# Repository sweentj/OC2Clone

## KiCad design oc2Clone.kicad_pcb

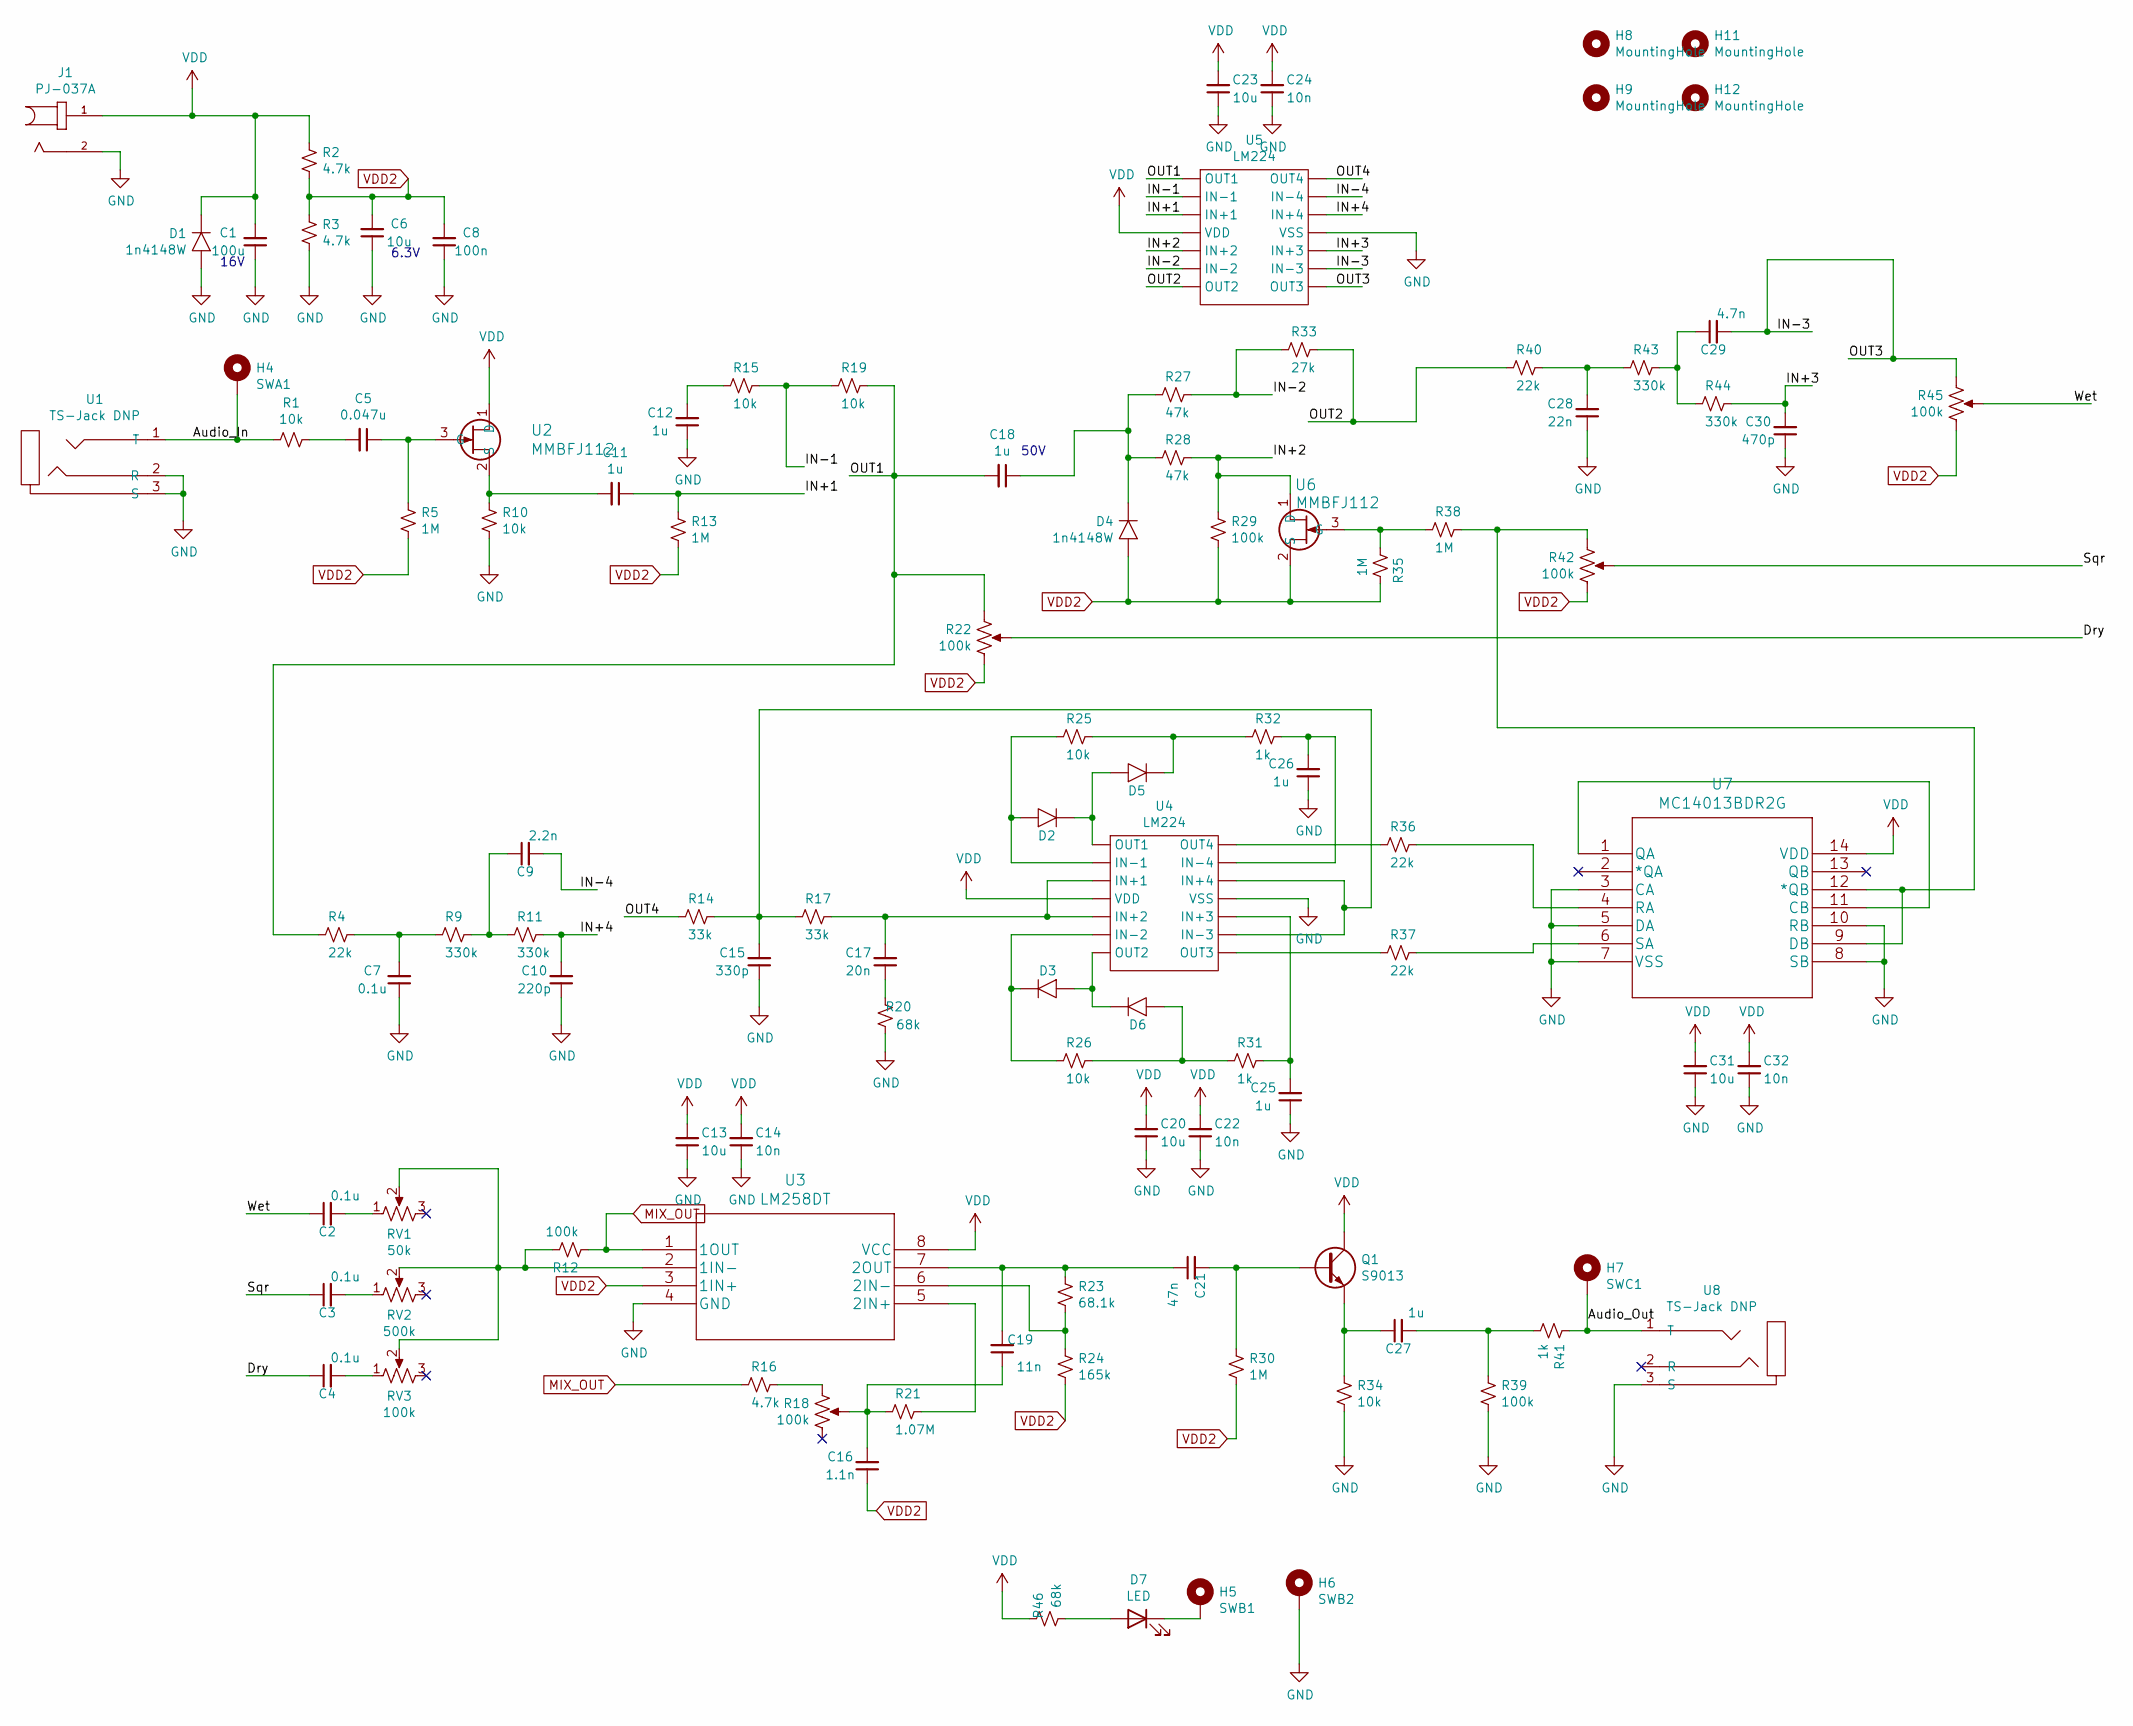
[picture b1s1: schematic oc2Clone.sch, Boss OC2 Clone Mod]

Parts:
C1: 100u; C_1210_3225Metric
C2, C3, C4, C7: 0.1u; C_0805_2012Metric
C5: 0.047u; C_0805_2012Metric
C6, C13, C20, C23, C31: 10u; C_0805_2012Metric
C8: 100n; C_0805_2012Metric
C9: 2.2n; C_0805_2012Metric
C10: 220p; C_0805_2012Metric
C11, C12, C18, C25, C26, C27: 1u; C_0805_2012Metric
C14, C22, C24, C32: 10n; C_0805_2012Metric
C15: 330p; C_0805_2012Metric
C16: 1.1n; C_0805_2012Metric
C17: 20n; C_0805_2012Metric
C19: 11n; C_0805_2012Metric
C21: 47n; C_0805_2012Metric
C28: 22n; C_0805_2012Metric
C29: 4.7n; C_0805_2012Metric
C30: 470p; C_0805_2012Metric
D1, D2, D3, D4, D5, D6: 1n4148W; SOD-123
D7: LED; LED_3mm_Radial
H4: SWA1; MountingHole_2.5mm_Pad
H5: SWB1; MountingHole_2.5mm_Pad
H6: SWB2; MountingHole_2.5mm_Pad
H7: SWC1; MountingHole_2.5mm_Pad
H8, H9, H11, H12: MountingHole; MountingHole_3.2mm_M3
J1: PJ-037A; CUI_PJ-037A
Q1: S9013; SOT-23
R1, R10, R15, R19, R25, R26, R34: 10k; R_0805_2012Metric
R2, R3, R16: 4.7k; R_0805_2012Metric
R4, R36, R37, R40: 22k; R_0805_2012Metric
R5, R13, R30, R35, R38: 1M; R_0805_2012Metric
R9, R11, R43, R44: 330k; R_0805_2012Metric
R12, R29, R39: 100k; R_0805_2012Metric
R14, R17: 33k; R_0805_2012Metric
R18, R22, R42, R45: 100k; Pot_RV16AF_Conn
R20, R46: 68k; R_0805_2012Metric
R21: 1.07M; R_0805_2012Metric
R23: 68.1k; R_0805_2012Metric
R24: 165k; R_0805_2012Metric
R27, R28: 47k; R_0805_2012Metric
R31, R32, R41: 1k; R_0805_2012Metric
R33: 27k; R_0805_2012Metric
RV1: 50k; Potentiometer_Bourns_TC33X_Vertical
RV2: 500k; Potentiometer_Bourns_TC33X_Vertical
RV3: 100k; Potentiometer_Bourns_TC33X_Vertical
U1, U8: TS-Jack DNP; TS-Jack
U2, U6: MMBFJ112; SOT-23
U3: LM258DT
U4, U5: LM224; SOIC-14_W3.9mm
U7: MC14013BDR2G; SOIC-14_W3.9mm

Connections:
/Audio_In: H4.1, R1.2, U1.1 (T)
/Audio_Out: H7.1, R41.2, U8.1 (T)
/Dry: C4.1, R22.2
/IN+1: C11.1, R13.2, U5.3 (IN+1)
/IN+2: R28.2, R29.2, U5.5 (IN+2), U6.1 (D)
/IN+3: C30.2, R44.2, U5.10 (IN+3)
/IN+4: C10.2, R11.2, U5.12 (IN+4)
/IN-1: R15.2, R19.1, U5.2 (IN-1)
/IN-2: R27.2, R33.1, U5.6 (IN-2)
/IN-3: C29.2, R45.1, U5.8 (OUT3), U5.9 (IN-3)
/IN-4: C9.2, U5.13 (IN-4)
/OUT1: C18.2, R4.1, R19.2, R22.1, U5.1 (OUT1)
/OUT2: R33.2, R40.1, U5.7 (OUT2)
/OUT4: R14.1, U5.14 (OUT4)
/Sqr: C3.1, R42.2
/Wet: C2.1, R45.2
GND: C1.1, C6.1, C7.1, C8.1, C10.1, C12.1, C13.1, C14.1, C15.1, C20.1, C22.1, C23.1, C24.1, C25.1, C26.1, C28.1, C30.1, C31.1, C32.1, D1.2, H6.1, J1.2, R3.1, R10.1, R20.2, R34.1, R39.1, U1.2 (R), U1.3 (S), U3.4 (GND), U4.11 (VSS), U5.11 (VSS), U7.3 (CA), U7.5 (DA), U7.7 (VSS), U7.8 (SB), U7.10 (RB), U8.3 (S)
MIX_OUT: R12.1, R16.1, U3.1 (1OUT)
unnamed: C2.2, RV1.1
unnamed: C3.2, RV2.1
unnamed: C4.2, RV3.1
unnamed: C5.1, R5.2, U2.3 (G)
unnamed: C5.2, R1.1
unnamed: C7.2, R4.2, R9.1
unnamed: C9.1, R9.2, R11.1
unnamed: C11.2, R10.2, U2.2 (S)
unnamed: C12.2, R15.1
unnamed: C15.2, R14.2, R17.1, U4.9 (IN-3), U4.12 (IN+4)
unnamed: C16.2, C19.1, R18.2, R21.1
unnamed: C17.1, R20.1
unnamed: C17.2, R17.2, U4.3 (IN+1), U4.5 (IN+2)
unnamed: C18.1, D4.1, R27.1, R28.1
unnamed: C19.2, C21.1, R23.2, U3.7 (2OUT)
unnamed: C21.2, Q1.1 (BASE_), R30.2
unnamed: C25.2, R31.2, U4.10 (IN+3)
unnamed: C26.2, R32.2, U4.13 (IN-4)
unnamed: C27.1, Q1.2 (EMITTER), R34.2
unnamed: C27.2, R39.2, R41.1
unnamed: C28.2, R40.2, R43.1
unnamed: C29.1, R43.2, R44.1
unnamed: D2.1, D5.2, U4.1 (OUT1)
unnamed: D2.2, R25.1, U4.2 (IN-1)
unnamed: D3.1, R26.1, U4.6 (IN-2)
unnamed: D3.2, D6.1, U4.7 (OUT2)
unnamed: D5.1, R25.2, R32.1
unnamed: D6.2, R26.2, R31.1
unnamed: D7.1 (K), H5.1
unnamed: D7.2 (A), R46.2
unnamed: R12.2, RV1.2, RV2.2, RV3.2, U3.2 (1IN-)
unnamed: R16.2, R18.1
unnamed: R21.2, U3.5 (2IN+)
unnamed: R23.1, R24.2, U3.6 (2IN-)
unnamed: R35.1, R38.1, U6.3 (G)
unnamed: R36.1, U4.14 (OUT4)
unnamed: R36.2, U7.4 (RA)
unnamed: R37.1, U4.8 (OUT3)
unnamed: R37.2, U7.6 (SA)
unnamed: R38.2, R42.1, U7.9 (DB), U7.12 (*QB)
unnamed: U7.1 (QA), U7.11 (CB)
VDD: C1.2, C13.2, C14.2, C20.2, C22.2, C23.2, C24.2, C31.2, C32.2, D1.1, J1.1, Q1.3 (COLLECTOR_(HEAT_SINK)_1), R2.2, R46.1, U2.1 (D), U3.8 (VCC), U4.4 (VDD), U5.4 (VDD), U7.14 (VDD)
VDD2: C6.2, C8.2, C16.1, D4.2, R2.1, R3.2, R5.1, R13.1, R22.3, R24.1, R29.1, R30.1, R35.2, R42.3, R45.3, U3.3 (1IN+), U6.2 (S)

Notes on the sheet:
6.3V
16V
50V

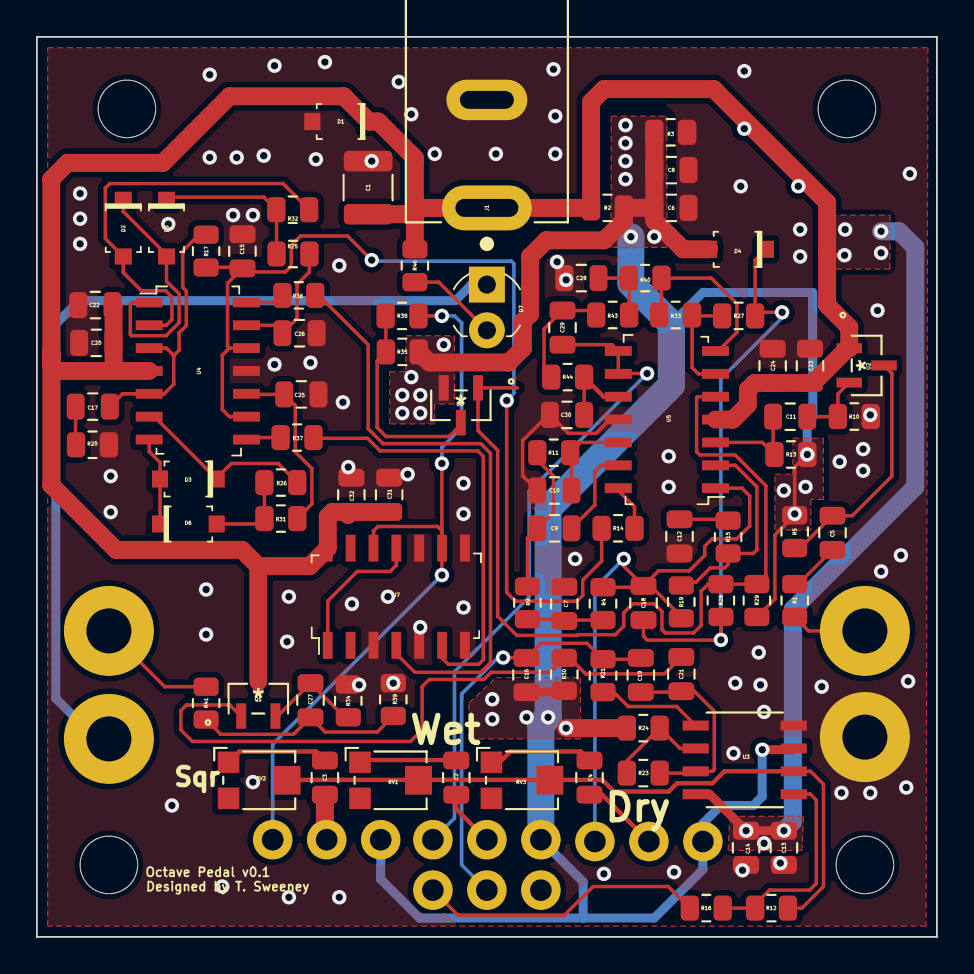
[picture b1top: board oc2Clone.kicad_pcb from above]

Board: 2 copper layers, 50.0 x 50.0 mm, 101 parts (0 on the bottom side), 61 nets.

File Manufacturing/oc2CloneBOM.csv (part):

value,footprint,datasheet,libsource/_lib,libsource/_part,libsource/_description,sheetpath/_names,sheetpath/_tstamps,tstamp,_ref,fields/field/0/_name,fields/field/0/__text,fields/field/1/_name,fields/field/1/__text
10k,oc2Clone:R_0805_2012Metric,~,Device,R_Small_US,"Resistor, small US symbol",/,/,61F28F26,R1,,,,
0.047u,oc2Clone:C_0805_2012Metric,~,Device,C_Small,"Unpolarized capacitor, small symbol",/,/,61F29AF7,C5,,,,
1M,oc2Clone:R_0805_2012Metric,~,Device,R_Small_US,"Resistor, small US symbol",/,/,61F2A248,R5,,,,
10k,oc2Clone:R_0805_2012Metric,~,Device,R_Small_US,"Resistor, small US symbol",/,/,61F2BE46,R10,,,,
MMBFJ112,oc2Clone:SOT-23,,oc2Clone,MMBFJ112,,/,/,61F46C64,U2,,,,
1M,oc2Clone:R_0805_2012Metric,~,Device,R_Small_US,"Resistor, small US symbol",/,/,61F475A0,R13,,,,
1u,oc2Clone:C_0805_2012Metric,~,Device,C_Small,"Unpolarized capacitor, small symbol",/,/,61F47CC3,C11,,,,
10k,oc2Clone:R_0805_2012Metric,~,Device,R_Small_US,"Resistor, small US symbol",/,/,61F4D295,R15,,,,
10k,oc2Clone:R_0805_2012Metric,~,Device,R_Small_US,"Resistor, small US symbol",/,/,61F4D862,R19,,,,
1u,oc2Clone:C_0805_2012Metric,~,Device,C_Small,"Unpolarized capacitor, small symbol",/,/,61F4DC3A,C12,,,,
PJ-037A,oc2Clone:CUI_PJ-037A,,oc2Clone,PJ-037A,,/,/,61F5BDD3,J1,MANUFACTURER,CUI INC,STANDARD,Manufacturer recommendations
4.7k,oc2Clone:R_0805_2012Metric,~,Device,R_Small_US,"Resistor, small US symbol",/,/,61F643DC,R2,,,,
1n4148W,oc2Clone:SOD-123,,oc2Clone,1n4148W,,/,/,61F64B75,D1,,,,
100u,oc2Clone:C_0805_2012Metric,~,Device,C_Small,"Unpolarized capacitor, small symbol",/,/,61F68953,C1,,,,
5.3k,oc2Clone:R_0805_2012Metric,~,Device,R_Small_US,"Resistor, small US symbol",/,/,61F6C5EB,R3,,,,
10u,oc2Clone:C_0805_2012Metric,~,Device,C_Small,"Unpolarized capacitor, small symbol",/,/,61F71DBA,C6,,,,
1u,oc2Clone:C_0805_2012Metric,~,Device,C_Small,"Unpolarized capacitor, small symbol",/,/,61F9DBBB,C18,,,,
MMBFJ112,oc2Clone:SOT-23,,oc2Clone,MMBFJ112,,/,/,61FBABA0,U6,,,,
1n4148W,oc2Clone:SOD-123,,oc2Clone,1n4148W,,/,/,61FBC9AA,D4,,,,
100k,oc2Clone:R_0805_2012Metric,~,Device,R_Small_US,"Resistor, small US symbol",/,/,61FBF013,R29,,,,
47k,oc2Clone:R_0805_2012Metric,~,Device,R_Small_US,"Resistor, small US symbol",/,/,61FC49C0,R27,,,,
47k,oc2Clone:R_0805_2012Metric,~,Device,R_Small_US,"Resistor, small US symbol",/,/,61FC4E33,R28,,,,
27k,oc2Clone:R_0805_2012Metric,~,Device,R_Small_US,"Resistor, small US symbol",/,/,61FE791F,R33,,,,
LM224,oc2Clone:SOIC-14_W3.9mm,,oc2Clone,LM224,,/,/,61F793F6,U4,,,,
1n4148W,oc2Clone:SOD-123,,oc2Clone,1n4148W,,/,/,61F9125F,D2,,,,
22k,oc2Clone:R_0805_2012Metric,~,Device,R_Small_US,"Resistor, small US symbol",/,/,61F9AB34,R4,,,,
0.1u,oc2Clone:C_0805_2012Metric,~,Device,C_Small,"Unpolarized capacitor, small symbol",/,/,61F9B54E,C7,,,,
330k,oc2Clone:R_0805_2012Metric,~,Device,R_Small_US,"Resistor, small US symbol",/,/,61F9CB72,R9,,,,
220p,oc2Clone:C_0805_2012Metric,~,Device,C_Small,"Unpolarized capacitor, small symbol",/,/,61FA2463,C10,,,,
330k,oc2Clone:R_0805_2012Metric,~,Device,R_Small_US,"Resistor, small US symbol",/,/,61FA2C1D,R11,,,,
2.2n,oc2Clone:C_0805_2012Metric,~,Device,C_Small,"Unpolarized capacitor, small symbol",/,/,61FB13AE,C9,,,,
33k,oc2Clone:R_0805_2012Metric,~,Device,R_Small_US,"Resistor, small US symbol",/,/,61FD912B,R14,,,,
330p,oc2Clone:C_0805_2012Metric,~,Device,C_Small,"Unpolarized capacitor, small symbol",/,/,61FD9131,C15,,,,
33k,oc2Clone:R_0805_2012Metric,~,Device,R_Small_US,"Resistor, small US symbol",/,/,61FD9137,R17,,,,
20n,oc2Clone:C_0805_2012Metric,~,Device,C_Small,"Unpolarized capacitor, small symbol",/,/,61FDF2D6,C17,,,,
68k,oc2Clone:R_0805_2012Metric,~,Device,R_Small_US,"Resistor, small US symbol",/,/,61FDFAAF,R20,,,,
10k,oc2Clone:R_0805_2012Metric,~,Device,R_Small_US,"Resistor, small US symbol",/,/,6201AA30,R25,,,,
1n4148W,oc2Clone:SOD-123,,oc2Clone,1n4148W,,/,/,6201EC3C,D5,,,,
1n4148W,oc2Clone:SOD-123,,oc2Clone,1n4148W,,/,/,6203C172,D3,,,,
10k,oc2Clone:R_0805_2012Metric,~,Device,R_Small_US,"Resistor, small US symbol",/,/,6203C17C,R26,,,,
1n4148W,oc2Clone:SOD-123,,oc2Clone,1n4148W,,/,/,6203C182,D6,,,,
1k,oc2Clone:R_0805_2012Metric,~,Device,R_Small_US,"Resistor, small US symbol",/,/,62078C9F,R32,,,,
1u,oc2Clone:C_0805_2012Metric,~,Device,C_Small,"Unpolarized capacitor, small symbol",/,/,620791CC,C26,,,,
1k,oc2Clone:R_0805_2012Metric,~,Device,R_Small_US,"Resistor, small US symbol",/,/,620AEF8D,R31,,,,
1u,oc2Clone:C_0805_2012Metric,~,Device,C_Small,"Unpolarized capacitor, small symbol",/,/,620AEF93,C25,,,,
22k,oc2Clone:R_0805_2012Metric,~,Device,R_Small_US,"Resistor, small US symbol",/,/,620FC65C,R36,,,,
22k,oc2Clone:R_0805_2012Metric,~,Device,R_Small_US,"Resistor, small US symbol",/,/,620FD094,R37,,,,
MC14013BDR2G,oc2Clone:SOIC-14_W3.9mm,,oc2Clone,MC14013BDR2G,,/,/,61FC6A71,U7,,,,
LM224,oc2Clone:SOIC-14_W3.9mm,,oc2Clone,LM224,,/,/,61F4A182,U5,,,,
S9013,oc2Clone:SOT-23,,oc2Clone,S9013,,/,/,61FE6156,Q1,,,,
10k,oc2Clone:R_0805_2012Metric,~,Device,R_Small_US,"Resistor, small US symbol",/,/,620001B3,R34,,,,
1u,oc2Clone:C_0805_2012Metric,~,Device,C_Small,"Unpolarized capacitor, small symbol",/,/,62002F5C,C27,,,,
TS-Jack DNP,oc2Clone:TS-Jack,,oc2Clone,TS-Jack,,/,/,6202D86E,U8,,,,
100k,oc2Clone:R_0805_2012Metric,~,Device,R_Small_US,"Resistor, small US symbol",/,/,62032039,R39,,,,
1k,oc2Clone:R_0805_2012Metric,~,Device,R_Small_US,"Resistor, small US symbol",/,/,6209A59D,R41,,,,
1M,oc2Clone:R_0805_2012Metric,~,Device,R_Small_US,"Resistor, small US symbol",/,/,620B683E,R30,,,,
100k,oc2Clone:Pot_RV16AF_Conn,,oc2Clone,RV16AF,,/,/,62029CE7,R22,,,,
22k,oc2Clone:R_0805_2012Metric,~,Device,R_Small_US,"Resistor, small US symbol",/,/,620E2413,R40,,,,
330k,oc2Clone:R_0805_2012Metric,~,Device,R_Small_US,"Resistor, small US symbol",/,/,620E26A0,R43,,,,
22n,oc2Clone:C_0805_2012Metric,~,Device,C_Small,"Unpolarized capacitor, small symbol",/,/,620E421E,C28,,,,
4.7n,oc2Clone:C_0805_2012Metric,~,Device,C_Small,"Unpolarized capacitor, small symbol",/,/,6210EC37,C29,,,,
330k,oc2Clone:R_0805_2012Metric,~,Device,R_Small_US,"Resistor, small US symbol",/,/,62120F38,R44,,,,
470p,oc2Clone:C_0805_2012Metric,~,Device,C_Small,"Unpolarized capacitor, small symbol",/,/,621215EF,C30,,,,
100k,oc2Clone:Pot_RV16AF_Conn,,oc2Clone,RV16AF,,/,/,622044FB,R45,,,,
LM258DT,oc2Clone:LM258DT,,oc2Clone,LM258DT,,/,/,622368D7,U3,,,,
100k,oc2Clone:Pot_RV16AF_Conn,,oc2Clone,RV16AF,,/,/,62058E43,R18,,,,
5k,oc2Clone:R_0805_2012Metric,~,Device,R_Small_US,"Resistor, small US symbol",/,/,6205A7B1,R16,,,,
68.1k,oc2Clone:R_0805_2012Metric,~,Device,R_Small_US,"Resistor, small US symbol",/,/,6208101E,R23,,,,
165k,oc2Clone:R_0805_2012Metric,~,Device,R_Small_US,"Resistor, small US symbol",/,/,62082F8F,R24,,,,
1.07M,oc2Clone:R_0805_2012Metric,~,Device,R_Small_US,"Resistor, small US symbol",/,/,62116F61,R21,,,,
11n,oc2Clone:C_0805_2012Metric,~,Device,C_Small,"Unpolarized capacitor, small symbol",/,/,62149583,C19,,,,
1.1n,oc2Clone:C_0805_2012Metric,~,Device,C_Small,"Unpolarized capacitor, small symbol",/,/,6219277B,C16,,,,
100k,oc2Clone:R_0805_2012Metric,~,Device,R_Small_US,"Resistor, small US symbol",/,/,6220D6F9,R12,,,,
0.1u,oc2Clone:C_0805_2012Metric,~,Device,C_Small,"Unpolarized capacitor, small symbol",/,/,6226ECB9,C2,,,,
0.1u,oc2Clone:C_0805_2012Metric,~,Device,C_Small,"Unpolarized capacitor, small symbol",/,/,62283D1D,C3,,,,
0.1u,oc2Clone:C_0805_2012Metric,~,Device,C_Small,"Unpolarized capacitor, small symbol",/,/,6228423F,C4,,,,
10k,oc2Clone:R_0805_2012Metric,~,Device,R_Small_US,"Resistor, small US symbol",/,/,622847E3,R6,,,,
500k,oc2Clone:R_0805_2012Metric,~,Device,R_Small_US,"Resistor, small US symbol",/,/,62284F19,R7,,,,
50k,oc2Clone:R_0805_2012Metric,~,Device,R_Small_US,"Resistor, small US symbol",/,/,622854D7,R8,,,,
1M,oc2Clone:R_0805_2012Metric,~,Device,R_Small_US,"Resistor, small US symbol",/,/,623819E5,R38,,,,
1M,oc2Clone:R_0805_2012Metric,~,Device,R_Small_US,"Resistor, small US symbol",/,/,623821EA,R35,,,,
100k,oc2Clone:Pot_RV16AF_Conn,,oc2Clone,RV16AF,,/,/,6243DF26,R42,,,,
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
